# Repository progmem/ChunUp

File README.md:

# ChunUp!

y'know, like the phrase 'tune up'

look

i thought it was a cute name alright

## What is ChunUp?

ChunUp is a variation of [48productions's Perpetual Free Credits PCB](https://github.com/48productions/Perpetual-Free-Credits-PCB). Like PFC, it keeps compatible games fully credited up at all times. Unlike PFC, ChunUp acts to be compatible with one, and only one game:

- Chunithm
- that's it, just Chunithm

ChunUp acts as a replacement to the coin mechanism in the Chunithm cab, allowing for nondestructive, reversible modification. The PCB is designed to be mounted onto a YLP-06V connector by crimping the connector's pins to bare (plastic removed) 0.1" "Dupont" pin headers.

## Disclaimer

As mentioned in 48productions's project:

> This project came about because of a few relevant conversations in the awesome western arcade rhythm game community, and the general concept/design was discussed by several community members.
> You are installing this board at your own risk, and I cannot be held liable for damages, destruction, magic smoke escaping, or otherwise.
> For arcade games on an official online network, your network may not allow the use of this board or similar mods. As such, usage of this board in these circumstances isn't recommended.
> *Any games mentioned are properties of their respective owners. This design was produced independently of them, and is in no way endorsed or officially supported.*

This project requires you have the parts and enough comfort to solder small surface-mount components (0603). Additionally, a crimper is necessary for joining the 0.1" Dupont pin to the JST YL pins. If you do not feel comfortable with soldering small parts or do not have the equipment or drive to crimp, it's advised to use 48productions's original project instead.

## How do I assemble this?

With the four plated holes oriented "up", solder the following 0603 components to these locations:

- 1k resistor, soldered to the top-left
- 56k resistor, soldered to the top-right
- 10uF ceramic capacitor (16V or higher), soldered to the bottom-left
- 5.6k resistor, soldered to the bottom-right

Next, solder the following components to their respective pads, with the dot on each part towards the top-left:

- Texas Instruments NE555PWR (or equivalent TSSOP-8 555 timer)
- onsemi FODM217C (or equivalent SOP-4 optocoupler)

Next, obtain the following parts for the connector:

- JST YLP-06V (the connector used for the coin mech)
- SYF-01T-P0.5A or SYF-41T-P0.5A pins (the socket pins used for this connector)
- At least four 0.1" Dupont header pins
  - It's advised to get the "longer" variant of these pins, intended for use in e.g. breadboards.

Separate the 0.1" Dupont header pins from their plastic retainer using e.g. a set of pliers. Crimp each bare-metal pin to one of the the socket pins. Once you have four pins prepared, orient the large retention tab on the JST YLP-06V "up" and install the crimped pins to the top-left, top-center, top-right, and bottom-left positions respectively (positions 1-4). The header pins should be sticking out of the connector.

Once installed, fit the ChunUp PCB onto the exposed header pins with the surface-mount pins facing away from the connector body (the ChunUp PCB should physically install only one way). Clip the header pins to length before soldering.

## How do I use it?

- Unplug the coin mech's 6-pin connector
- Plug in ChunUp

## How does this work?

This board leverages power from the coin blocker relay on the Chunithm cab. When the game is in a state to accept coins, power is normally supplied to a mechanism that allows the cabinet to accept coins. Once the maximum credit limit in Chunithm is reached (24), power disengages, which causes the mechanism to reject future credits.

ChunUp uses the power normally going to the coin blocker relay to drive a 555 timer. The 555 timer is configured to supply coin pulses that repeatedly trigger the game's coin switch. This is done with an optoisolator in order to keep the coin switch line separated from the rest of the power supply. When the optoisolator is "activated", it connects the coin switch line to ground, similar to how the microswitch on a coin mechanism functions.

Once the game is at the maximum credit limit, Chunithm disengages power to the coin blocker relay (cutting power from the 555 and the optoisolator), which stops the insertion of coins. Once a coin is "spent", ChunUp will re-engage after a short delay.

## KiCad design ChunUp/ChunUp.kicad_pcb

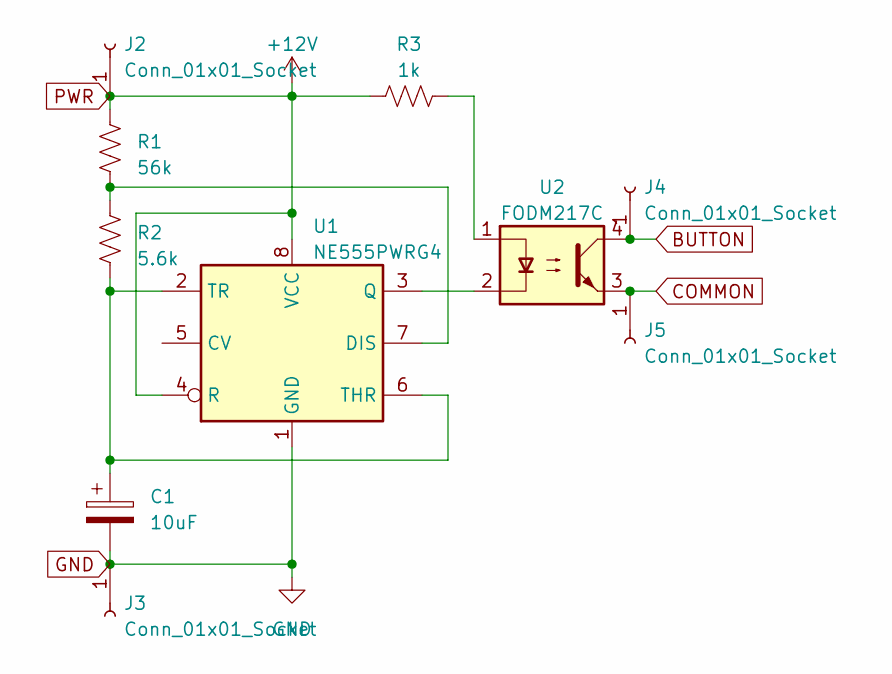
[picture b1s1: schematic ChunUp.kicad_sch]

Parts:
C1: 10uF; C_0603_1608Metric_Pad1.08x0.95mm_HandSolder
J2, J3, J4, J5: Conn_01x01_Socket; PinHeader_1x01_P2.54mm_Vertical
R1: 56k; R_0603_1608Metric_Pad0.98x0.95mm_HandSolder
R2: 5.6k; R_0603_1608Metric_Pad0.98x0.95mm_HandSolder
R3: 1k; R_0603_1608Metric_Pad0.98x0.95mm_HandSolder
U1: NE555PWRG4; TSSOP-8_4.4x3mm_P0.65mm
U2: FODM217C; SOP-4_4.4x2.6mm_P1.27mm

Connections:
BUTTON: J4.1, U2.4
COMMON: J5.1, U2.3
GND: C1.2, J3.1, U1.1 (GND)
unnamed: R3.2, U2.1
unnamed: R1.2, R2.1, U1.7 (DIS)
unnamed: U1.3 (Q), U2.2
unnamed: C1.1, R2.2, U1.2 (TR), U1.6 (THR)
PWR: J2.1, R1.1, R3.1, U1.4 (R), U1.8 (VCC)

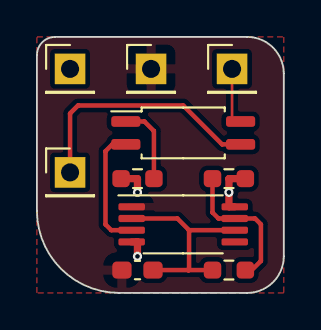
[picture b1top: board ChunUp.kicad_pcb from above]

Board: 2 copper layers, 13.7 x 14.2 mm, 10 parts (0 on the bottom side), 8 nets.

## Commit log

2023-08-03 Initial commit of ChunUp, the very small version of PFC
2024-05-09 Add additional documentation
2024-05-09 Crop image
